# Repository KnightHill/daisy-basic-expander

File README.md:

# ElectroSmith POD basic expander

[ElectroSmith POD](https://www.electro-smith.com/daisy/pod)

Adds two potentiometers and six buttons to the pod. Check the included KiCad 7 [schematics](hardware) for details.

 # Disclamer

This is a hobby project. I accept no responsibility for damage to you Daisy Seed, external equipment or anything else. You use this code and harware at your own risk.

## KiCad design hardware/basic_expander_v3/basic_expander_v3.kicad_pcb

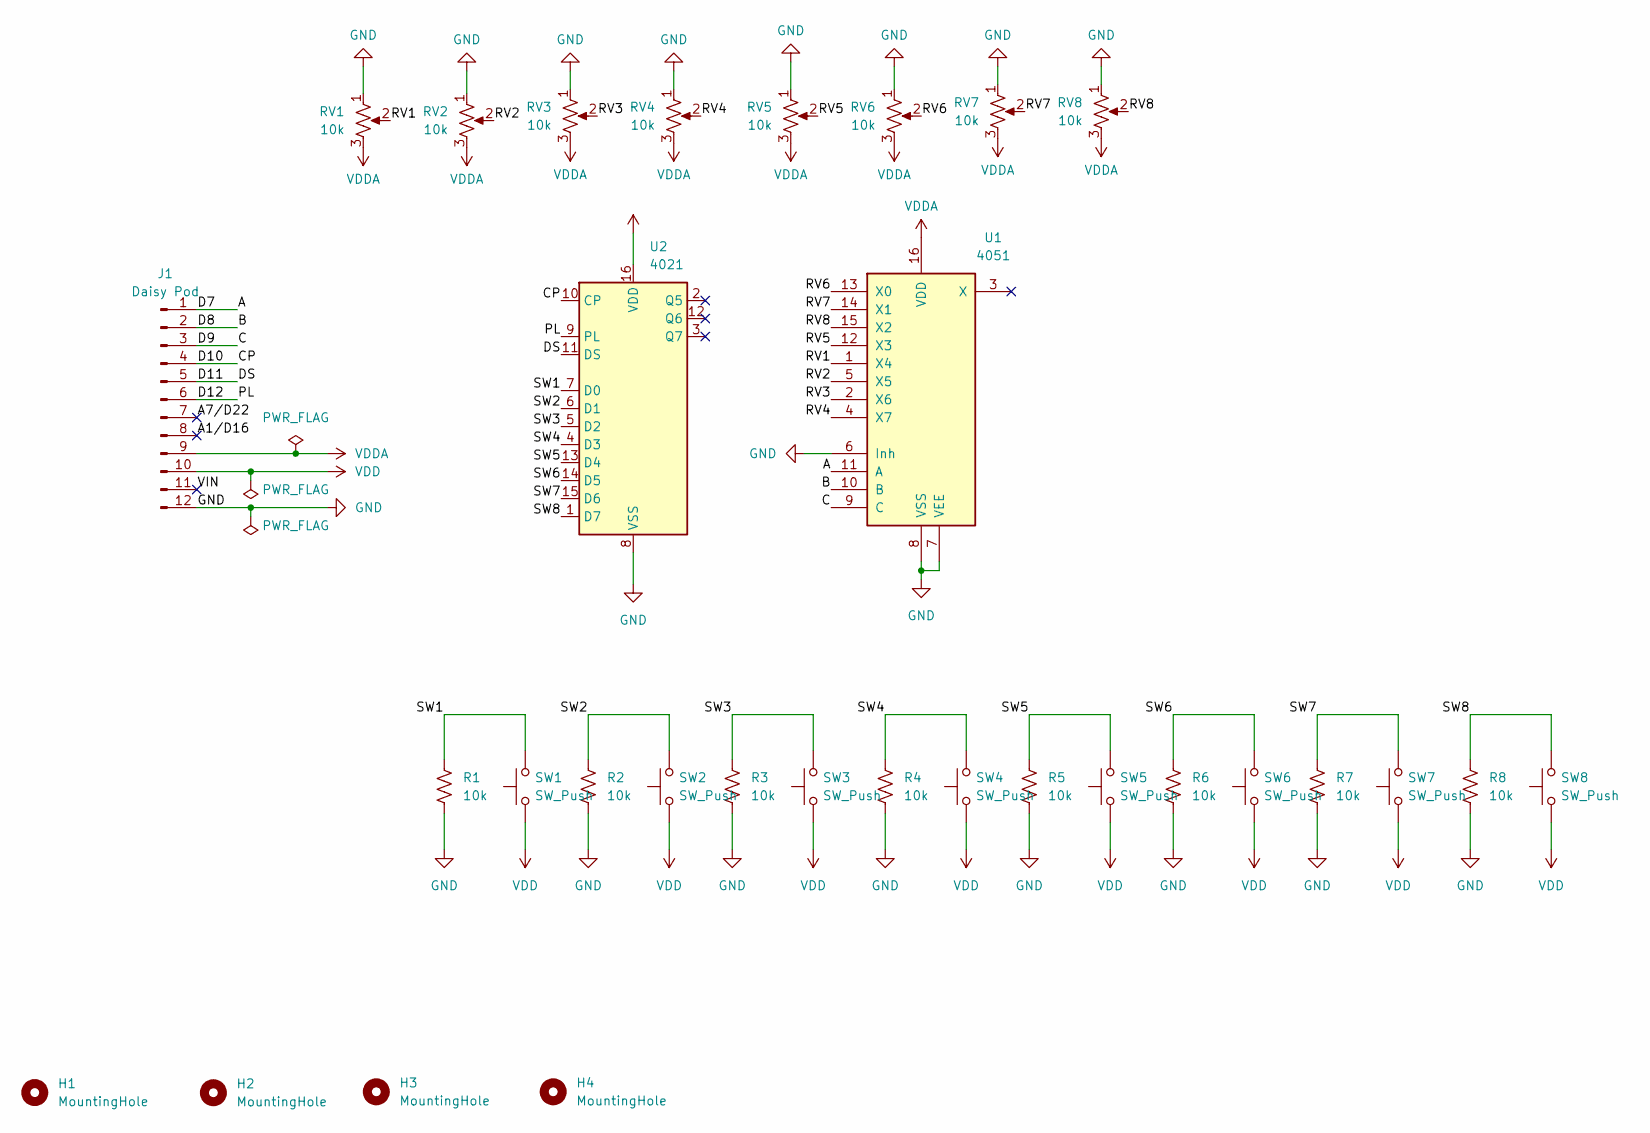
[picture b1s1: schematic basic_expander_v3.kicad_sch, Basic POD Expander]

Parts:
H1, H2, H3, H4: MountingHole; MountingHole_2.2mm_M2
J1: Daisy Pod; PinHeader_1x12_P2.54mm_Vertical
R1, R2, R3, R4, R5, R6, R7, R8: 10k; R_Axial_DIN0207_L6.3mm_D2.5mm_P7.62mm_Horizontal
RV1, RV2, RV3, RV4, RV5, RV6, RV7, RV8: 10k; Potentiometer_Alpha_RD901F-40-00D_Single_Vertical
SW1, SW2, SW3, SW4, SW5, SW6, SW7, SW8: SW_Push; SW_PUSH_6mm
U1: 4051; DIP-16_W7.62mm
U2: 4021; DIP-16_W7.62mm

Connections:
/A: J1.1, U1.11 (A)
/A1/D16: J1.8
/A7/D22: J1.7
/B: J1.2, U1.10 (B)
/C: J1.3, U1.9 (C)
/CP: J1.4, U2.10 (CP)
/D11: J1.5, U2.11 (DS)
/D12: J1.6, U2.9 (PL)
/RV1: RV1.2, U1.1 (X4)
/RV2: RV2.2, U1.5 (X5)
/RV3: RV3.2, U1.2 (X6)
/RV4: RV4.2, U1.4 (X7)
/RV5: RV5.2, U1.12 (X3)
/RV6: RV6.2, U1.13 (X0)
/RV7: RV7.2, U1.14 (X1)
/RV8: RV8.2, U1.15 (X2)
/SW1: R1.1, SW1.2, U2.7 (D0)
/SW2: R2.1, SW2.2, U2.6 (D1)
/SW3: R3.1, SW3.2, U2.5 (D2)
/SW4: R4.1, SW4.2, U2.4 (D3)
/SW5: R5.1, SW5.2, U2.13 (D4)
/SW6: R6.1, SW6.2, U2.14 (D5)
/SW7: R7.1, SW7.2, U2.15 (D6)
/SW8: R8.1, SW8.2, U2.1 (D7)
/VIN: J1.11
GND: J1.12, R1.2, R2.2, R3.2, R4.2, R5.2, R6.2, R7.2, R8.2, RV1.1, RV2.1, RV3.1, RV4.1, RV5.1, RV6.1, RV7.1, RV8.1, U1.6 (Inh), U1.7 (VEE), U1.8 (VSS), U2.8 (VSS)
VDD: J1.10, SW1.1, SW2.1, SW3.1, SW4.1, SW5.1, SW6.1, SW7.1, SW8.1, U2.16 (VDD)
VDDA: J1.9, RV1.3, RV2.3, RV3.3, RV4.3, RV5.3, RV6.3, RV7.3, RV8.3, U1.16 (VDD)

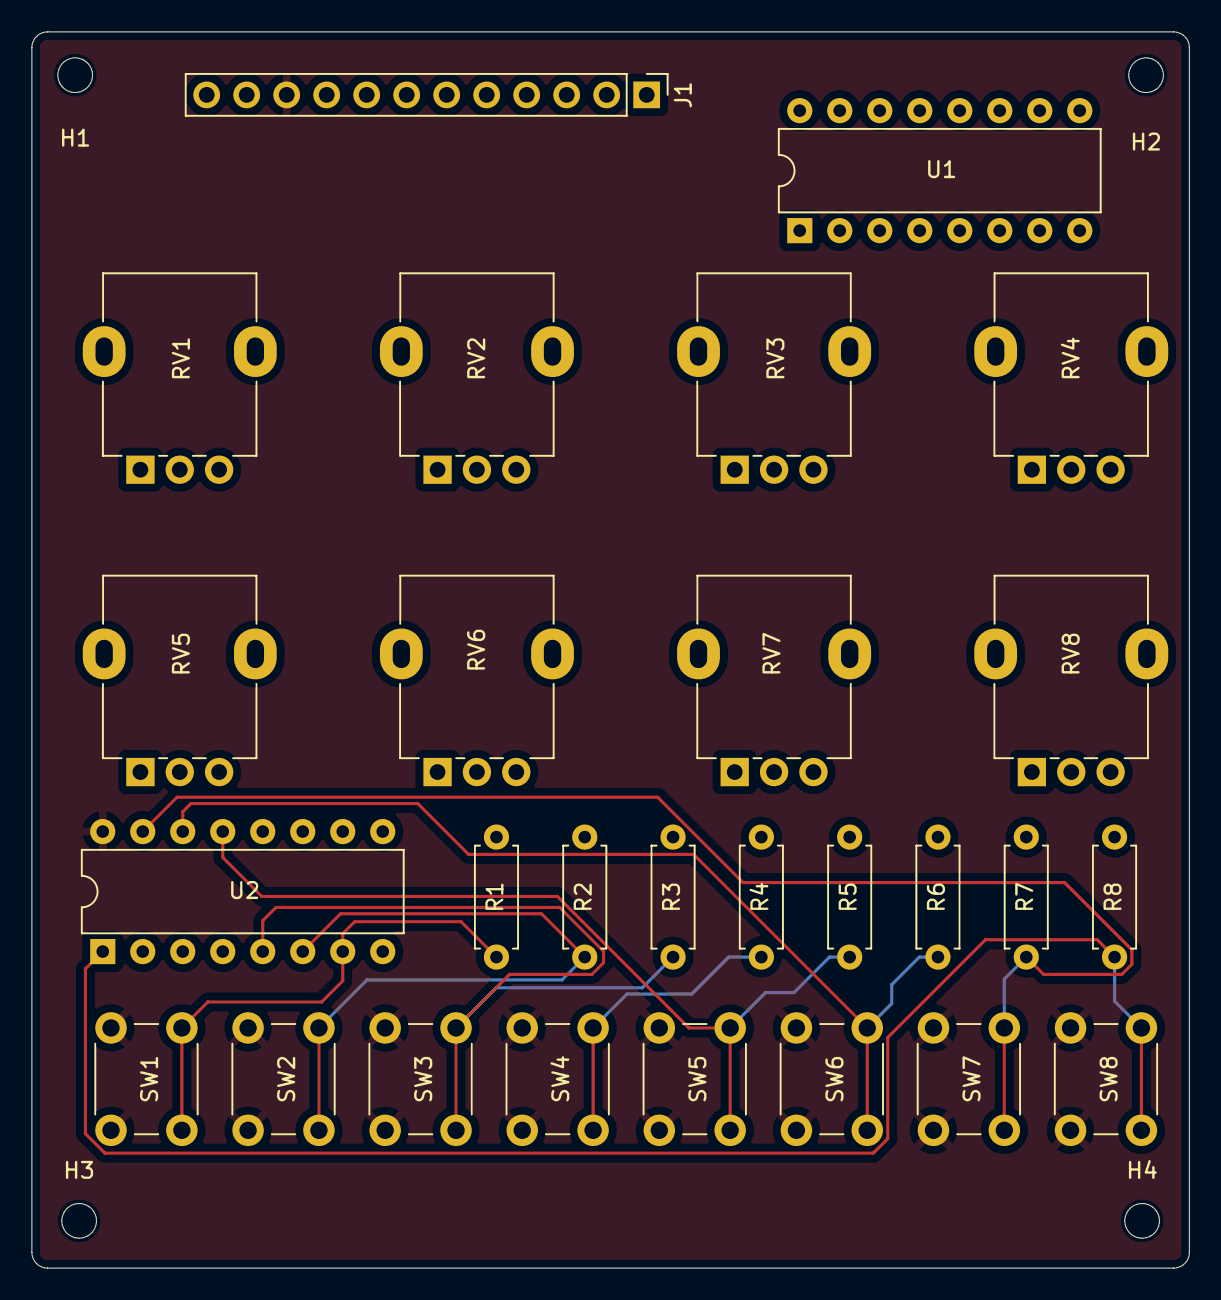
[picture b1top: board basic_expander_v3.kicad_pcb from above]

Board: 2 copper layers, 73.5 x 78.5 mm, 31 parts (0 on the bottom side), 25 nets.

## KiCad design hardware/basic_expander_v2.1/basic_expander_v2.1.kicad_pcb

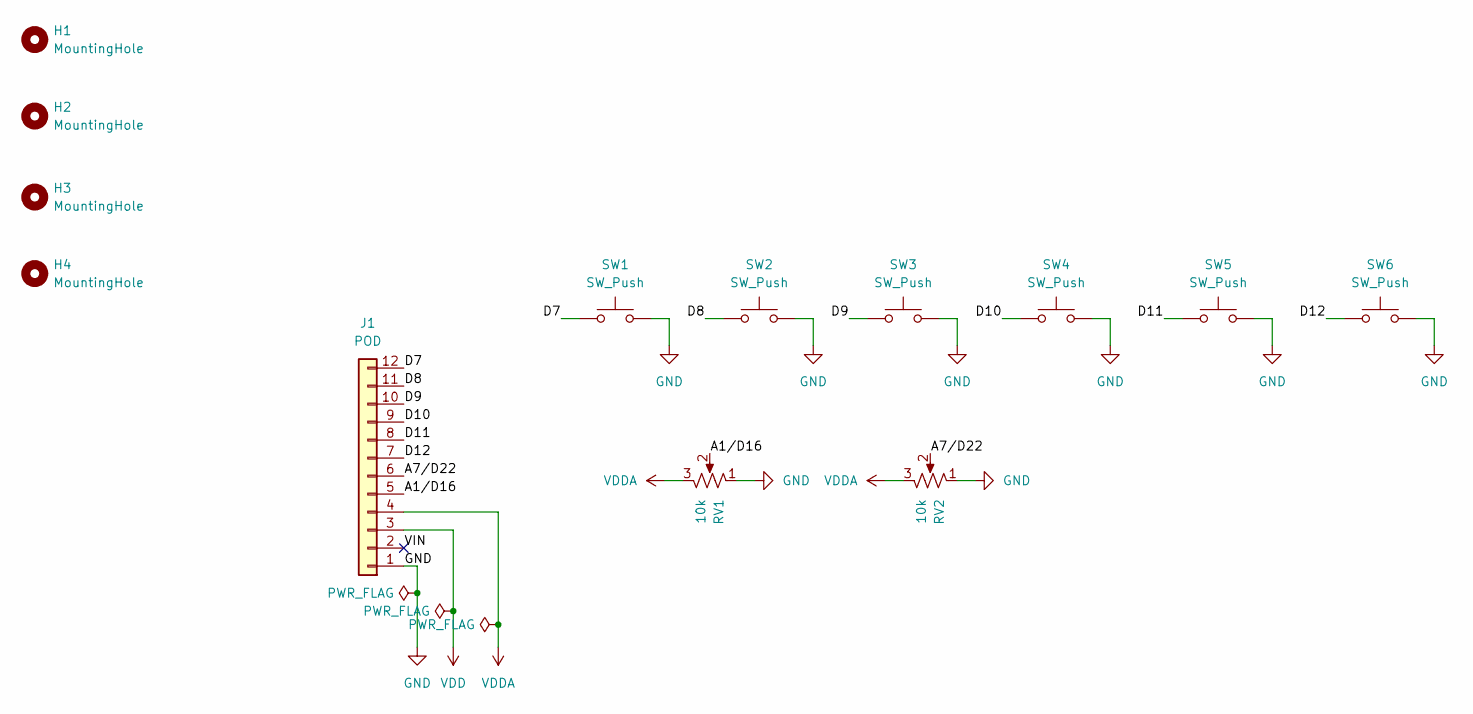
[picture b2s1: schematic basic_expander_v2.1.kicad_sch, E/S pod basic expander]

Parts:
H1, H2, H3, H4: MountingHole; MountingHole_2.2mm_M2
J1: POD; PinHeader_1x12_P2.54mm_Vertical
RV1, RV2: 10k; Potentiometer_uxcel_9mm_Single_Vertical
SW1, SW2, SW3, SW4, SW5, SW6: SW_Push; SW_PUSH_6mm

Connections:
/A1/D16: J1.5, RV1.2
/A7/D22: J1.6, RV2.2
/D7: J1.12, SW1.1
/D8: J1.11, SW2.1
/D9: J1.10, SW3.1
/D10: J1.9, SW4.1
/D11: J1.8, SW5.1
/D12: J1.7, SW6.1
/VIN: J1.2
GND: J1.1, RV1.1, RV2.1, SW1.2, SW2.2, SW3.2, SW4.2, SW5.2, SW6.2
VDD: J1.3
VDDA: J1.4, RV1.3, RV2.3

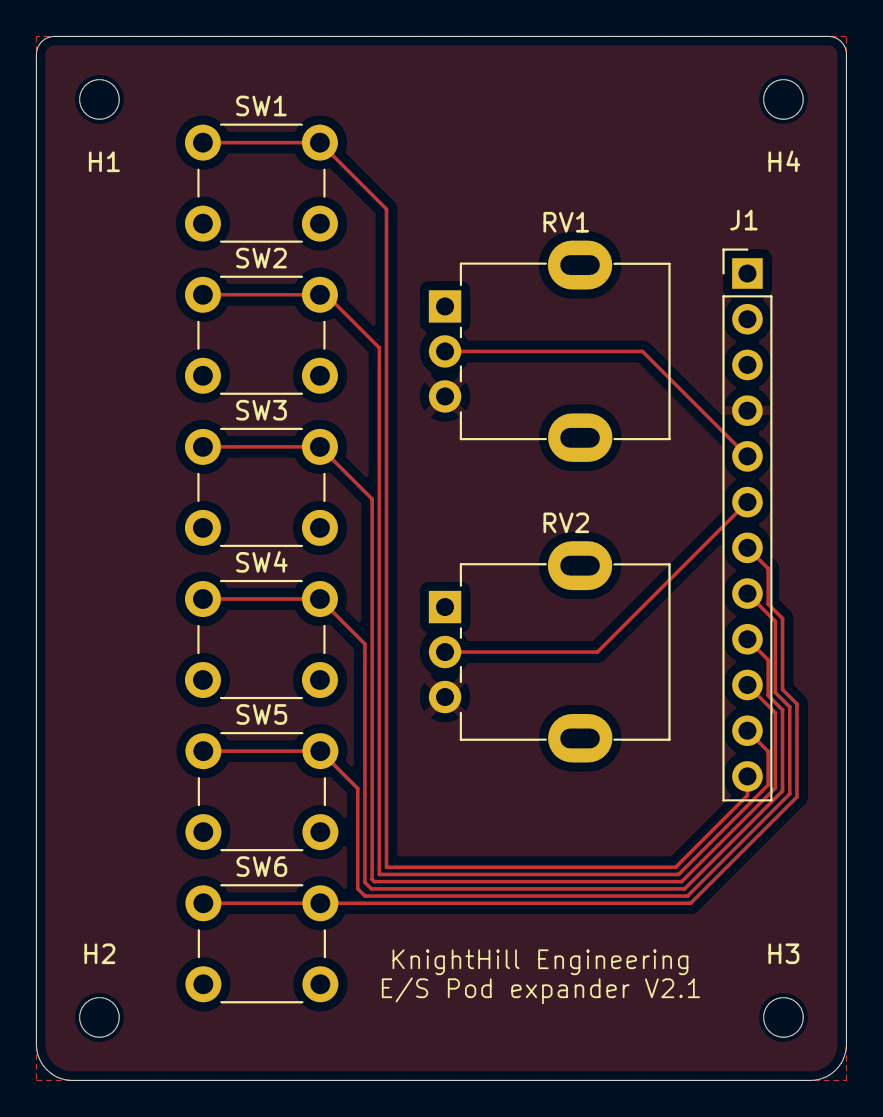
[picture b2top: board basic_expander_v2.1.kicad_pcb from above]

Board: 2 copper layers, 45.0 x 58.0 mm, 13 parts (0 on the bottom side), 10 nets.

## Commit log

2023-08-27 add schematic
2023-08-31 Improve schematic
2023-08-31 change folder name
2023-08-31 add readme
2023-08-31 improve readme
2023-12-06 PCB changes
2023-12-07 pcd changes
2023-12-08 Add basic_exp files
2023-12-09 Makefile changes
2023-12-09 readme changes
2023-12-19 cleanup
2023-12-19 Add gerber/drill files
2023-12-19 gerber files cleanup
2023-12-25 add v3 pcb
2023-12-30 add two more buttons
2023-12-30 add debug
2023-12-30 switch knob 3 and 4
2023-12-30 add pcb v2.1
2023-12-30 remove old files
2024-01-02 fix pots orientation
2024-01-02 add v2.1 gerber files
2024-01-03 add v3 files
2024-01-03 add 4 pots
2024-01-04 add disclamer
2024-01-07 add license
